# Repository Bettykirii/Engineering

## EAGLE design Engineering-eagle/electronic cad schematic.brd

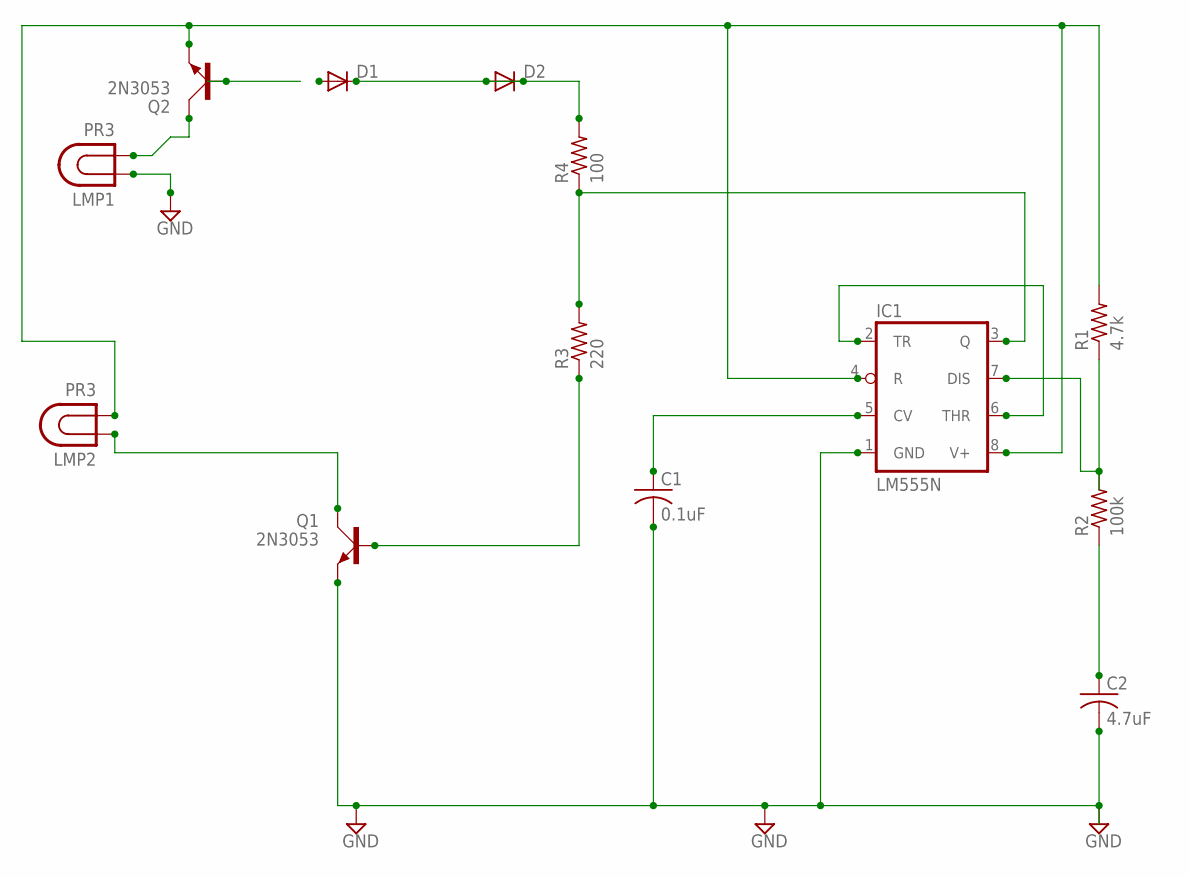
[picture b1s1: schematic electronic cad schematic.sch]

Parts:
C1: 0.1uF; C050-025X075
C2: 4.7uF; C025_050-025X075
D1, D2: DIODE-D-2.5; D-2.5
IC1: LM555N; DIL08
LMP1, LMP2: PR3; LDH-5R
Q1, Q2: 2N3053; TO39
R1: 4.7k; 0207/2V
R2: 100k; 0207/2V
R3: 220; 0207/2V
R4: 100; 0207/2V

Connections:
GND: C1.2, C2.2, IC1.1 (GND), LMP1.1, Q1.1 (E)
unnamed: IC1.4 (R), IC1.8 (V+), LMP2.2, Q2.1 (E), R1.2
unnamed: C2.1, R2.1
unnamed: IC1.7 (DIS), R1.1
unnamed: D1.C, D2.A, D2.C, R4.2
unnamed: LMP2.1, Q1.3 (C)
unnamed: IC1.2 (TR), IC1.6 (THR)
unnamed: Q1.2 (B), R3.1
unnamed: LMP1.2, Q2.3 (C)
unnamed: C1.1, IC1.5 (CV)
unnamed: IC1.3 (Q), R3.2, R4.1

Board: 2 copper layers, 13 parts (0 on the bottom side), 11 nets, no tracks yet.

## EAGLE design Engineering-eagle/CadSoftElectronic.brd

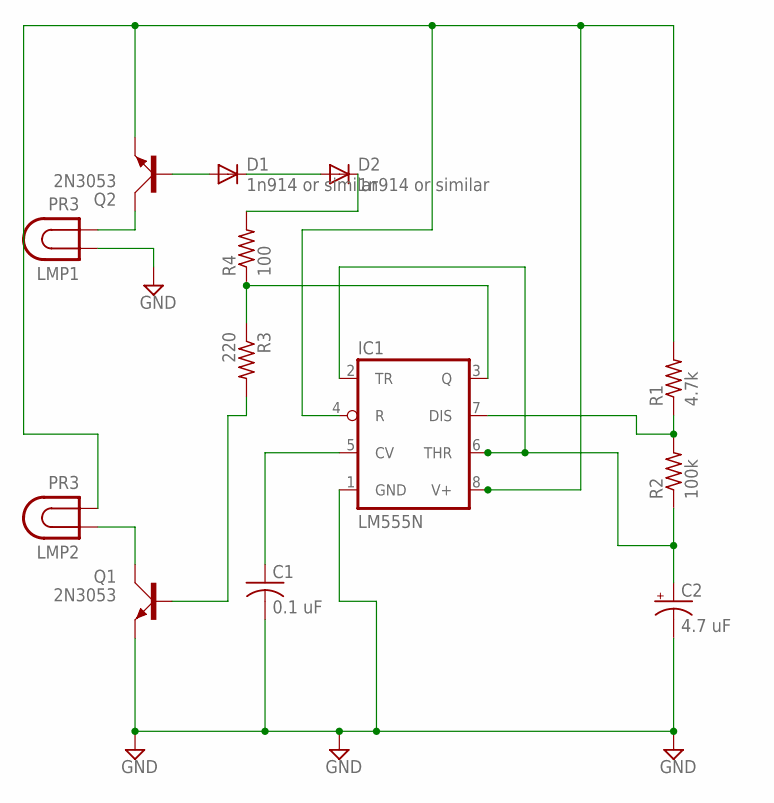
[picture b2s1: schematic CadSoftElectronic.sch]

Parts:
C1: 0.1 uF; C050-025X075
C2: 4.7 uF; E5-5
D1, D2: 1n914 or similar; D-2.5
IC1: LM555N; DIL08
LMP1, LMP2: PR3; LDH-5R
Q1, Q2: 2N3053; TO39
R1: 4.7k; 0207/2V
R2: 100k; 0207/2V
R3: 220; 0207/2V
R4: 100; 0207/2V

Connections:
GND: C1.2, C2.-, IC1.1 (GND), LMP1.1, Q1.1 (E)
unnamed: IC1.4 (R), IC1.8 (V+), LMP2.2, Q2.1 (E), R1.2
unnamed: LMP2.1, Q1.3 (C)
unnamed: IC1.7 (DIS), R1.1, R2.2
unnamed: C2.+, IC1.2 (TR), IC1.6 (THR), R2.1
unnamed: C1.1, IC1.5 (CV)
unnamed: D1.C, D2.A
unnamed: D2.C, R4.2
unnamed: IC1.3 (Q), R3.1, R4.1
unnamed: LMP1.2, Q2.3 (C)
unnamed: D1.A, Q2.2 (B)
unnamed: Q1.2 (B), R3.2

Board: 2 copper layers, 13 parts (0 on the bottom side), 12 nets, no tracks yet.

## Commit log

2017-11-07 hardware commit
